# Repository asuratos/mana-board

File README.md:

# The Mana Board

A small, simple leverless controller. Powered by a Raspberry Pi Pico running [GP2040-CE](https://github.com/OpenStickCommunity/GP2040-CE).

Named as such because the the shape reminded me of a cutting board (Japanese:まな板 ***mana**-ita*).

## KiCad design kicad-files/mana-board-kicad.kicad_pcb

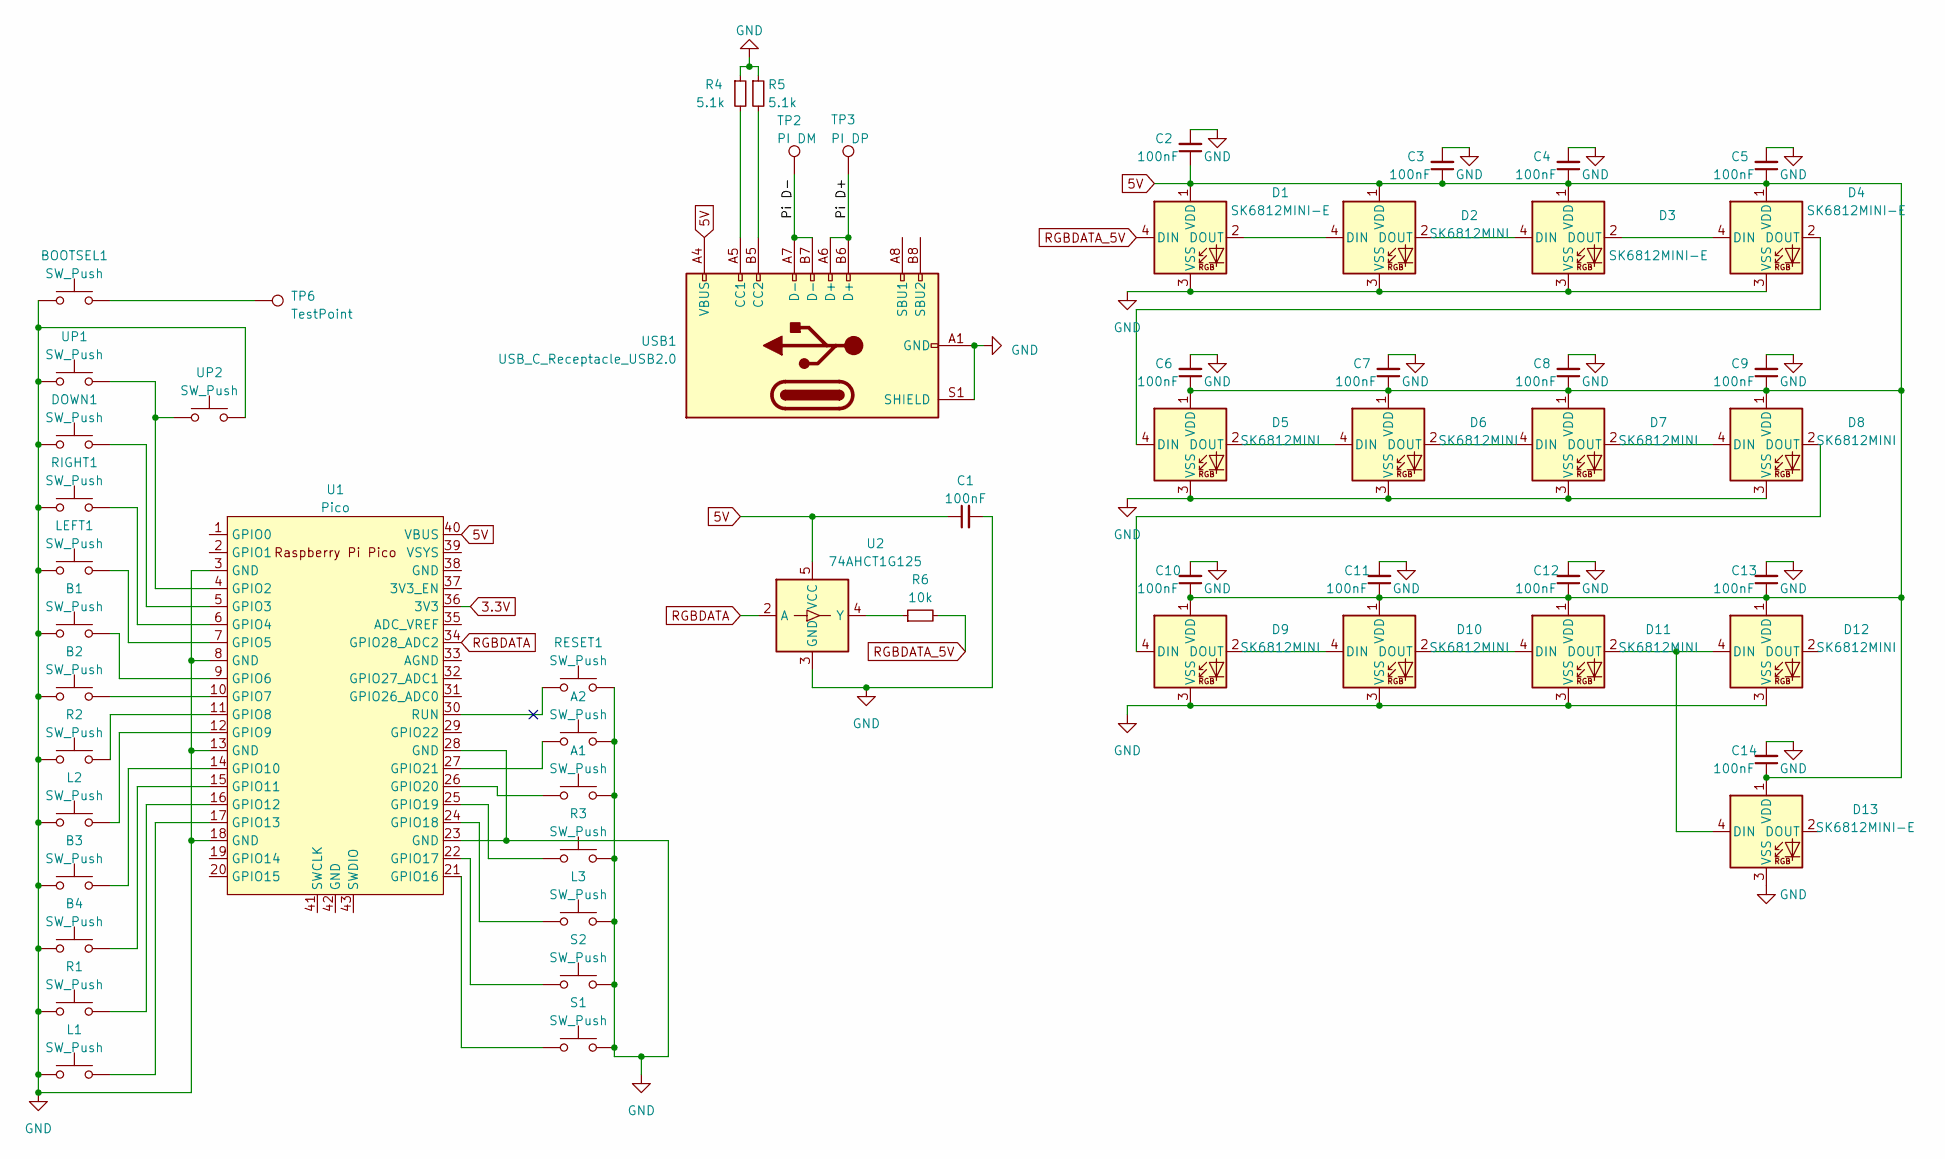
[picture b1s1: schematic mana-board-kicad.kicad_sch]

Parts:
A1, A2: SW_Push; SW_PUSH_6mm_H4.3mm
B1, B2, B3, B4: SW_Push; SW_Kailh_Choc_V2
BOOTSEL1: SW_Push; SW_Push_1P1T_XKB_TS-1187A
C1, C2, C3, C4, C5, C6, C7, C8, C9, C10, C11, C12, C13, C14: 100nF; C_1206_3216Metric_Pad1.33x1.80mm_HandSolder
D1, D3, D4, D13: SK6812MINI-E; SK6812-MINI-E
D2, D5, D6, D7, D8, D9, D10, D11, D12: SK6812MINI; SK6812-MINI-E
DOWN1: SW_Push; SW_Kailh_Choc_V2
L1, L2: SW_Push; SW_Kailh_Choc_V2
L3: SW_Push; SW_PUSH_6mm_H4.3mm
LEFT1: SW_Push; SW_Kailh_Choc_V2
R1, R2: SW_Push; SW_Kailh_Choc_V2
R3: SW_Push; SW_PUSH_6mm_H4.3mm
R4, R5: 5.1k; R_1206_3216Metric_Pad1.30x1.75mm_HandSolder
R6: 10k; R_1206_3216Metric_Pad1.30x1.75mm_HandSolder
RESET1: SW_Push; SW_Push_1P1T_XKB_TS-1187A
RIGHT1: SW_Push; SW_Kailh_Choc_V2
S1, S2: SW_Push; SW_PUSH_6mm_H4.3mm
TP2: PI DM; TestPoint_THTPad_1.0x1.0mm_Drill0.5mm
TP3: PI DP; TestPoint_THTPad_1.0x1.0mm_Drill0.5mm
TP6: TestPoint; TestPoint_THTPad_1.0x1.0mm_Drill0.5mm
U1: Pico; RPi_Pico_SMD_TH
U2: 74AHCT1G125; SOT-23-5
UP1, UP2: SW_Push; SW_Kailh_Choc_V2
USB1: USB_C_Receptacle_USB2.0; USB_C_Receptacle_GCT_USB4105-xx-A_16P_TopMnt_Horizontal

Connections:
3.3V: U1.36 (3V3)
5V: C1.1, C2.1, C3.1, C4.1, C5.1, C6.1, C7.1, C8.1, C9.1, C10.1, C11.1, C12.1, C13.1, C14.1, D1.1 (VDD), D2.1 (VDD), D3.1 (VDD), D4.1 (VDD), D5.1 (VDD), D6.1 (VDD), D7.1 (VDD), D8.1 (VDD), D9.1 (VDD), D10.1 (VDD), D11.1 (VDD), D12.1 (VDD), D13.1 (VDD), U1.40 (VBUS), U2.5 (VCC), USB1.A4 (VBUS), USB1.A9 (VBUS), USB1.B4 (VBUS), USB1.B9 (VBUS)
/Pi D+: TP3.1, USB1.A6 (D+), USB1.B6 (D+)
/Pi D-: TP2.1, USB1.A7 (D-), USB1.B7 (D-)
GND: A1.2, A2.2, B1.1, B2.1, B3.1, B4.1, BOOTSEL1.1, C1.2, C2.2, C3.2, C4.2, C5.2, C6.2, C7.2, C8.2, C9.2, C10.2, C11.2, C12.2, C13.2, C14.2, D1.3 (VSS), D2.3 (VSS), D3.3 (VSS), D4.3 (VSS), D5.3 (VSS), D6.3 (VSS), D7.3 (VSS), D8.3 (VSS), D9.3 (VSS), D10.3 (VSS), D11.3 (VSS), D12.3 (VSS), D13.3 (VSS), DOWN1.1, L1.1, L2.1, L3.2, LEFT1.1, R1.1, R2.1, R3.2, R4.1, R5.1, RESET1.2, RIGHT1.1, S1.2, S2.2, U1.3 (GND), U1.8 (GND), U1.13 (GND), U1.18 (GND), U1.23 (GND), U1.28 (GND), U2.3 (GND), UP1.1, UP2.2, USB1.A1 (GND), USB1.A12 (GND), USB1.B1 (GND), USB1.B12 (GND), USB1.S1 (SHIELD)
unnamed: BOOTSEL1.2, TP6.1
unnamed: D1.2 (DOUT), D2.4 (DIN)
unnamed: D2.2 (DOUT), D3.4 (DIN)
unnamed: D3.2 (DOUT), D4.4 (DIN)
unnamed: D4.2 (DOUT), D5.4 (DIN)
unnamed: D5.2 (DOUT), D6.4 (DIN)
unnamed: D6.2 (DOUT), D7.4 (DIN)
unnamed: D7.2 (DOUT), D8.4 (DIN)
unnamed: D8.2 (DOUT), D9.4 (DIN)
unnamed: D9.2 (DOUT), D10.4 (DIN)
unnamed: D10.2 (DOUT), D11.4 (DIN)
unnamed: D11.2 (DOUT), D12.4 (DIN), D13.4 (DIN)
unnamed: U1.4 (GPIO2), UP1.2, UP2.1
unnamed: DOWN1.2, U1.5 (GPIO3)
unnamed: RIGHT1.2, U1.6 (GPIO4)
unnamed: LEFT1.2, U1.7 (GPIO5)
unnamed: B1.2, U1.9 (GPIO6)
unnamed: B2.2, U1.10 (GPIO7)
unnamed: R2.2, U1.11 (GPIO8)
unnamed: L2.2, U1.12 (GPIO9)
unnamed: B3.2, U1.14 (GPIO10)
unnamed: B4.2, U1.15 (GPIO11)
unnamed: R1.2, U1.16 (GPIO12)
unnamed: L1.2, U1.17 (GPIO13)
unnamed: S1.1, U1.21 (GPIO16)
unnamed: S2.1, U1.22 (GPIO17)
unnamed: L3.1, U1.24 (GPIO18)
unnamed: R3.1, U1.25 (GPIO19)
unnamed: A1.1, U1.26 (GPIO20)
unnamed: A2.1, U1.27 (GPIO21)
unnamed: RESET1.1, U1.30 (RUN)
unnamed: R6.1, U2.4 (Y)
unnamed: R4.2, USB1.A5 (CC1)
unnamed: R5.2, USB1.B5 (CC2)
RGBDATA: U1.34 (GPIO28_ADC2), U2.2 (A)
RGBDATA_5V: D1.4 (DIN), R6.2

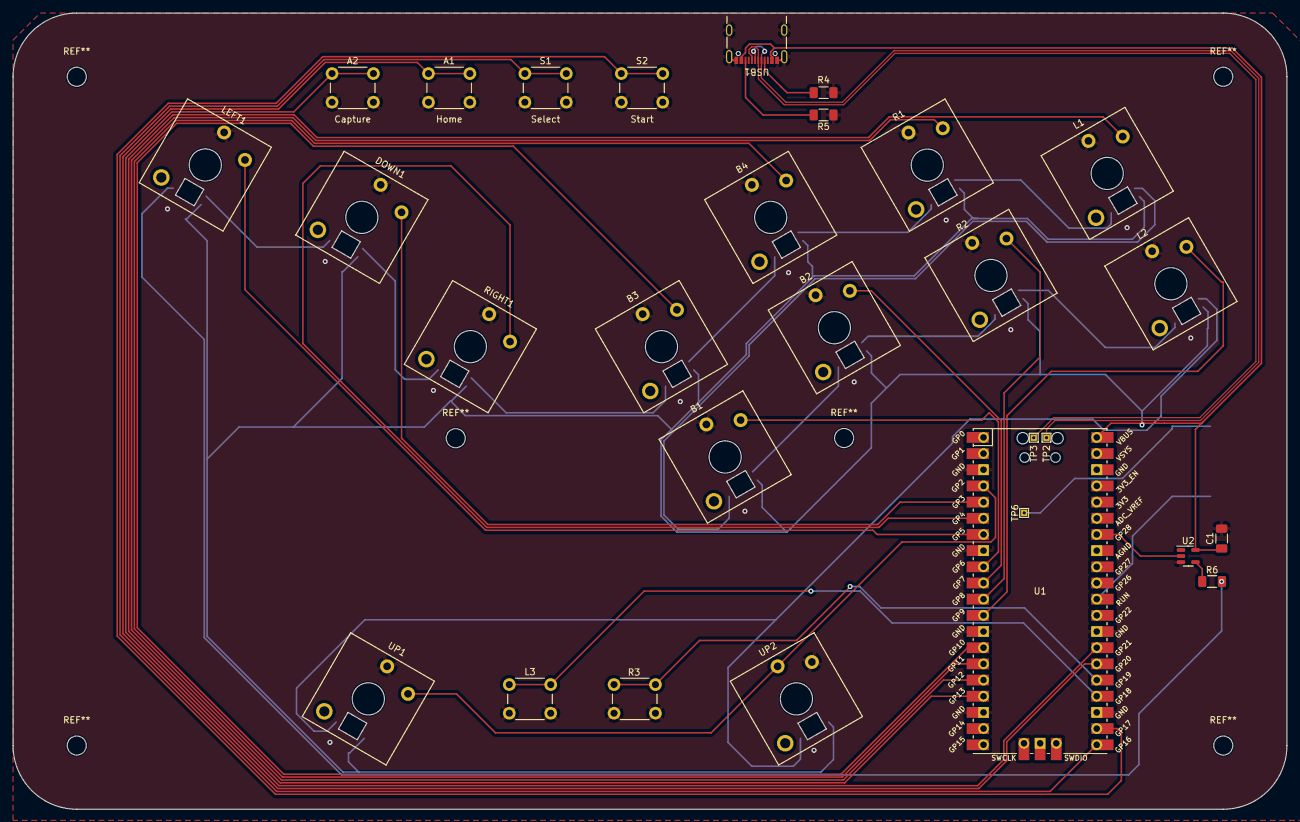
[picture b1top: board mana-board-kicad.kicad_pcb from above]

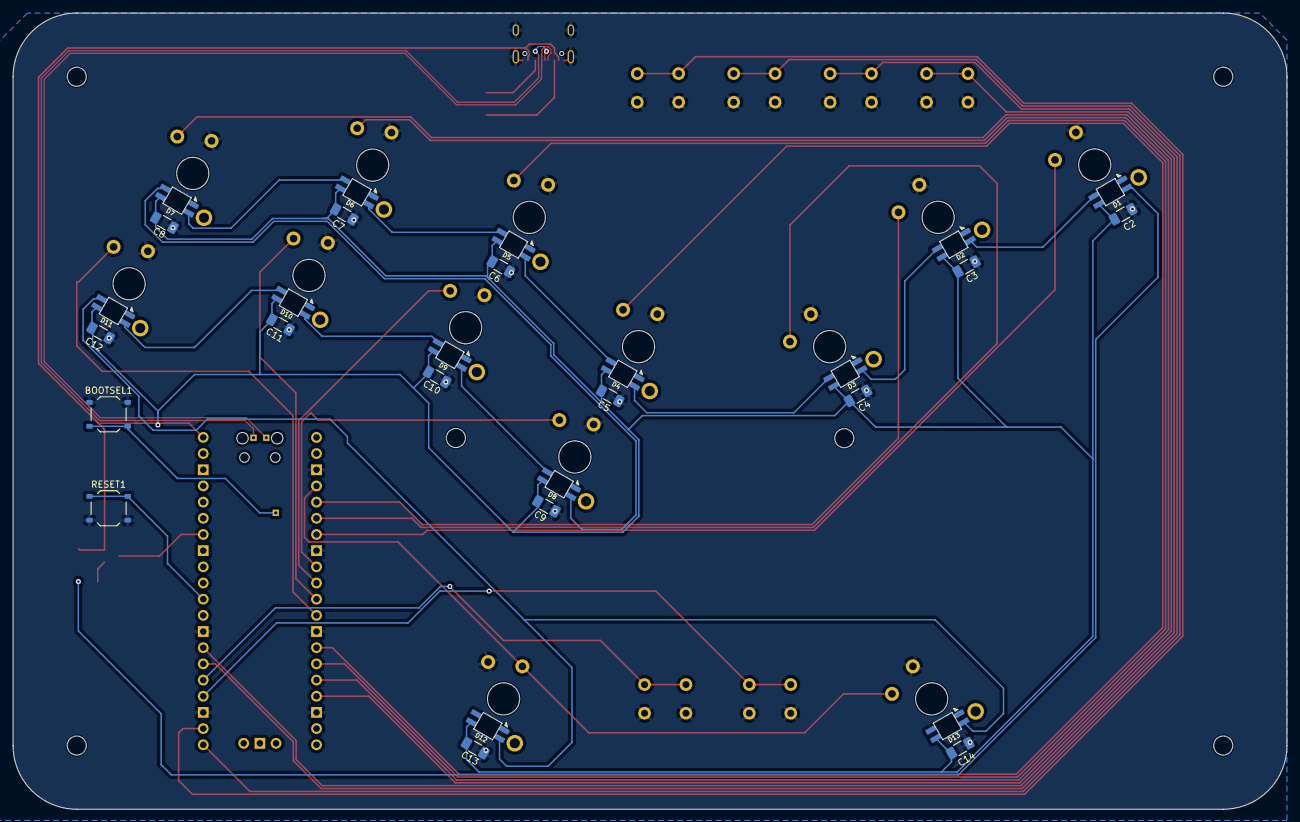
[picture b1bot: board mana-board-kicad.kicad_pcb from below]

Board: 2 copper layers, 200.0 x 125.0 mm, 57 parts (28 on the bottom side), 40 nets.

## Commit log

2023-06-17 Organize libraries, start rev1
2023-06-18 First pass at wiring rev1
2023-06-19 generate gerbers
2023-06-19 update board a little
2023-06-22 rev1 sent for prototyping
2023-06-28 Reroute USB data lines to remove via near USB C receptacle
2023-06-28 din't stage the correct file
2023-07-04 Change mounting holes to M3, separate LED Data line
2023-07-04 Cleaned up routing, cleanup todo
2023-07-05 Move parallel UP LEDs to the end of the LED chain
2023-07-05 reasign capacitor numbers
2023-07-07 renamed gerber subfolder
